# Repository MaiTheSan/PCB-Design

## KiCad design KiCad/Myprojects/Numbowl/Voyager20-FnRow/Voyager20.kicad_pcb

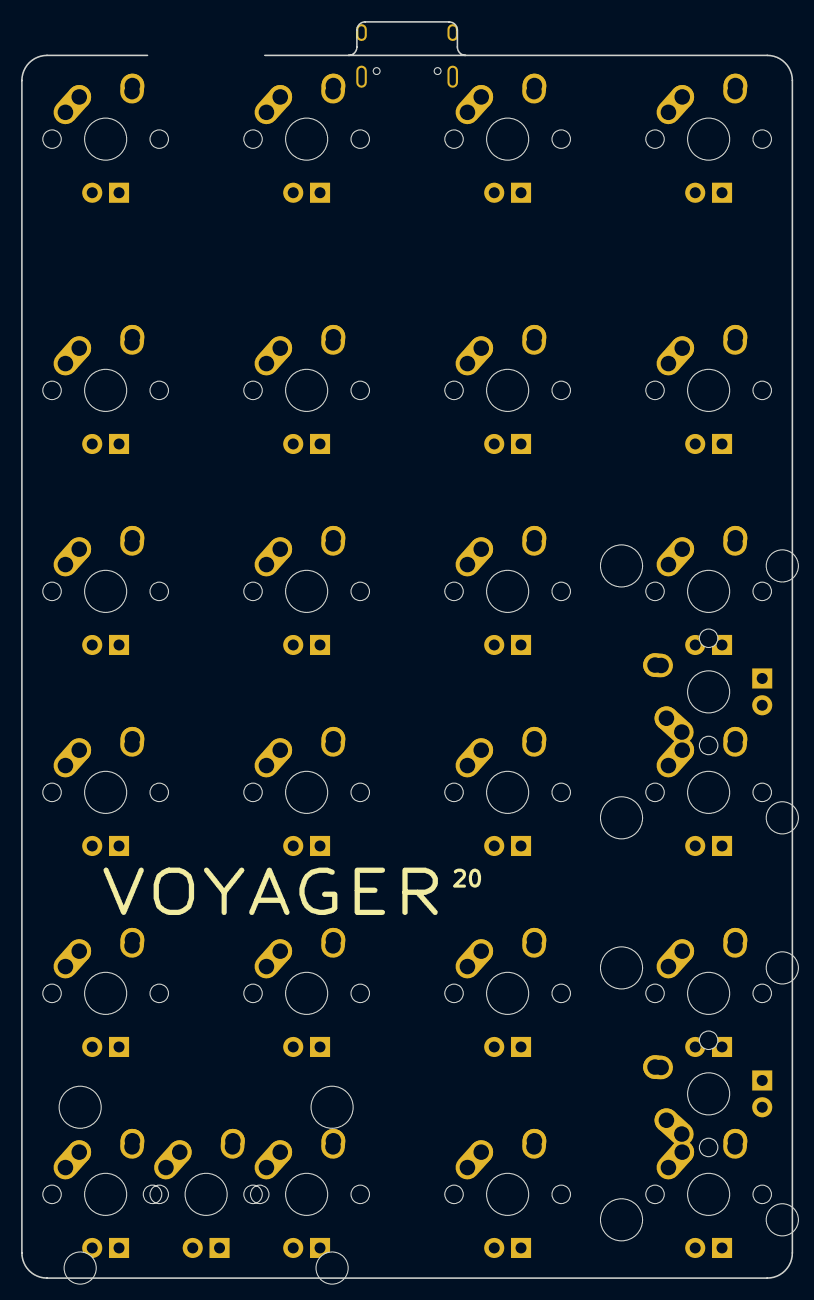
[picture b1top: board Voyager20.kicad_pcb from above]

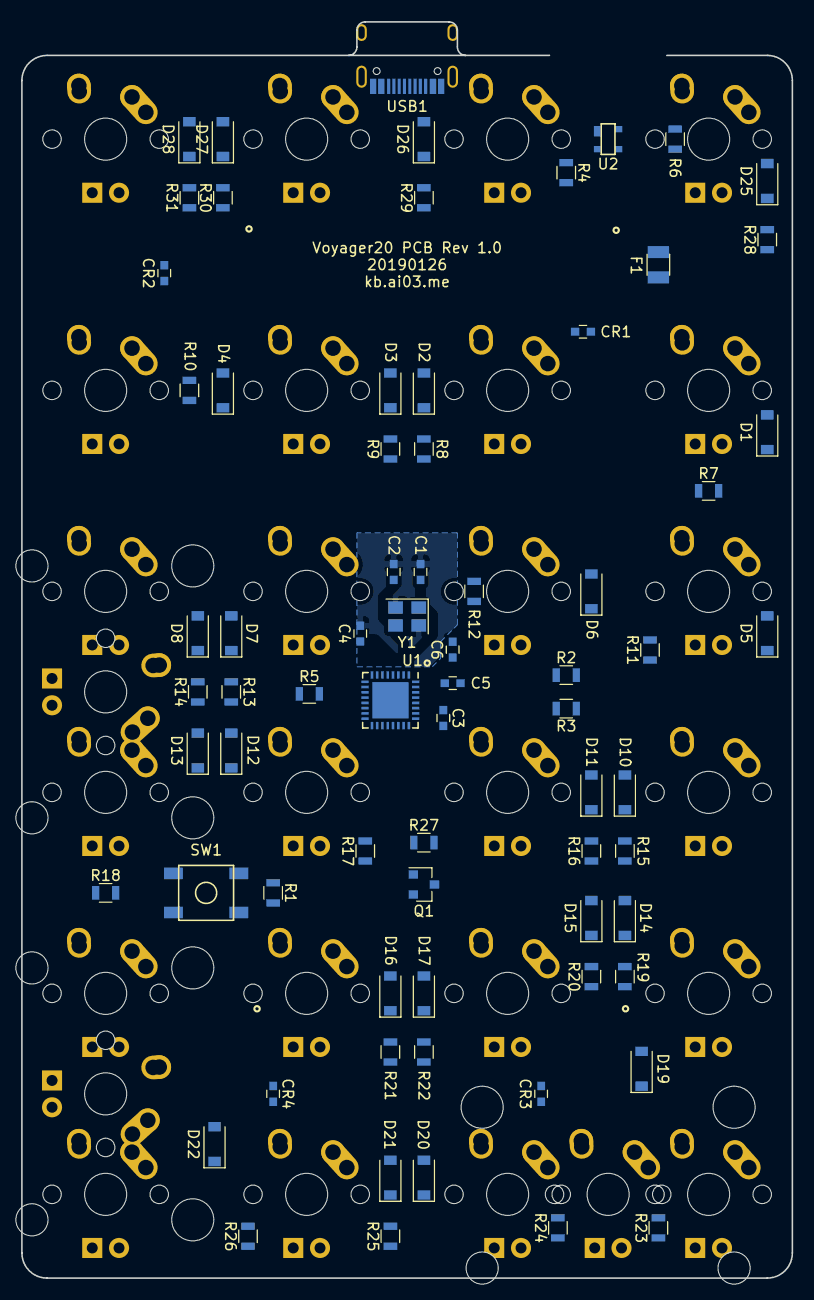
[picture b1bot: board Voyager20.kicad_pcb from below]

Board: 2 copper layers, 73.0 x 119.1 mm, 99 parts (72 on the bottom side), 75 nets, no tracks yet.

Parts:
C1, C2: 22p; C_0603
C3: 1uF; C_0603
C4, C5: 0.1u; C_0603
C6: 4.7u; C_0603
CR1, CR2, CR3, CR4: 0.1u; C_0603
D1, D2, D3, D4, D5, D6, D7, D8, D10, D11, D12, D13, D14, D15, D16, D17, D19, D20, D21, D22, D25, D26, D27, D28: SOD-123; D_SOD-123
F1: 500mA; Fuse_SMD1206_Reflow
MX1, MX2, MX3, MX4, MX5, MX6, MX7, MX8, MX9, MX10, MX11, MX12, MX13, MX14, MX15, MX16, MX17, MX18, MX19, MX20, MX21, MX22, MX23, MX24: MX-1U
MX-E-1, MX-E-2, MX-E-3: MX-2U; MX-2U-ReversedStabilizers
Q1: Q_NPN_BEC; SOT-23
R1, R5: 10k; R_0805
R2, R3: 22; R_0805
R4, R6: 5.1k; R_0805
R7, R8, R9, R10, R11, R12, R13, R14, R15, R16, R17, R18, R19, R20, R21, R22, R23, R24, R25, R26, R27, R28, R29, R30, R31: 1k; R_0805
SW1: SW_Push; SKQG-1155865
U1: ATmega32U2-AU; QFN-32-1EP_5x5mm_Pitch0.5mm
U2: PRTR5V0U2X; SOT143B
USB1: HRO-TYPE-C-31-M-12; HRO-TYPE-C-31-M-12-Assembly
Y1: 16MHz; Crystal_SMD_3225-4pin_3.2x2.5mm

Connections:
+5V: C4.1, C5.1, C6.1, CR1.1, CR2.1, CR3.1, CR4.1, F1.1, MX1.3, MX2.3, MX3.3, MX4.3, MX5.3, MX6.3, MX7.3, MX8.3, MX9.3, MX10.3, MX11.3, MX12.3, MX13.3, MX14.3, MX15.3, MX16.3, MX17.3, MX18.3, MX19.3, MX20.3, MX21.3, MX22.3, MX23.3, MX24.3, MX-E-1.3, MX-E-2.3, MX-E-3.3, R1.1, U1.4, U1.31, U1.32
COL0: MX1.1, MX5.1, MX9.1, MX13.1, MX17.1, MX21.1, MX-E-3.1, U1.26
COL1: MX2.1, MX6.1, MX10.1, MX14.1, MX18.1, MX22.1, U1.25
COL2: MX3.1, MX7.1, MX11.1, MX15.1, MX19.1, MX23.1, U1.17
COL3: MX4.1, MX8.1, MX12.1, MX16.1, MX20.1, MX24.1, MX-E-1.1, MX-E-2.1, U1.16
D+: R3.2, U1.29
D-: R2.1, U1.30
GND: C1.2, C2.2, C3.2, C4.2, C5.2, C6.2, CR1.2, CR2.2, CR3.2, CR4.2, Q1.2, R4.2, R5.1, R6.2, SW1.1, U1.3, U1.28, U2.1, USB1.1, USB1.12, USB1.13, Y1.2, Y1.4
LEDGND: Q1.3, R7.2, R8.2, R9.2, R10.2, R11.2, R12.2, R13.2, R14.2, R15.2, R16.2, R17.2, R18.2, R19.2, R20.2, R21.2, R22.2, R23.2, R24.2, R25.2, R26.2, R28.2, R29.2, R30.2, R31.2
unnamed: C1.1, U1.1, Y1.1
unnamed: C2.1, U1.2, Y1.3
unnamed: C3.1, U1.27
unnamed: D1.2, MX1.2
unnamed: D2.2, MX2.2
unnamed: D3.2, MX3.2
unnamed: D4.2, MX4.2
unnamed: D5.2, MX5.2
unnamed: D6.2, MX6.2
unnamed: D7.2, MX7.2
unnamed: D8.2, MX8.2
unnamed: D10.2, MX9.2
unnamed: D11.2, MX10.2
unnamed: D12.2, MX11.2
unnamed: D13.2, MX12.2, MX-E-1.2
unnamed: D14.2, MX13.2
unnamed: D15.2, MX14.2
unnamed: D16.2, MX15.2
unnamed: D17.2, MX16.2
unnamed: D19.2, MX17.2, MX-E-3.2
unnamed: D20.2, MX18.2
unnamed: D21.2, MX19.2
unnamed: D22.2, MX20.2, MX-E-2.2
unnamed: D25.2, MX21.2
unnamed: D26.2, MX22.2
unnamed: D27.2, MX23.2
unnamed: D28.2, MX24.2
unnamed: MX1.4, R7.1
unnamed: MX2.4, R8.1
unnamed: MX3.4, R9.1
unnamed: MX4.4, R10.1
unnamed: MX5.4, R11.1
unnamed: MX6.4, R12.1
unnamed: MX7.4, R13.1
unnamed: MX8.4, R14.1
unnamed: MX9.4, R15.1
unnamed: MX10.4, R16.1
unnamed: MX11.4, R17.1
unnamed: MX13.4, R19.1
unnamed: MX14.4, R20.1
unnamed: MX15.4, R21.1
unnamed: MX16.4, R22.1
unnamed: MX18.4, R24.1
unnamed: MX19.4, R25.1
unnamed: MX21.4, R28.1
unnamed: MX22.4, R29.1
unnamed: MX23.4, R30.1
unnamed: MX24.4, R31.1
unnamed: MX12.4, MX-E-1.4, R18.1
unnamed: MX20.4, MX-E-2.4, R26.1
unnamed: MX17.4, MX-E-3.4, R23.1
unnamed: Q1.1, R27.1
unnamed: R1.2, SW1.2, U1.24
unnamed: R2.2, U2.3, USB1.5, USB1.7
unnamed: R3.1, U2.2, USB1.6, USB1.8
unnamed: R4.1, USB1.10
unnamed: R5.2, U1.13
unnamed: R6.1, USB1.4
unnamed: R27.2, U1.21
ROW0: D1.1, D2.1, D3.1, D4.1, U1.7
ROW1: D5.1, D6.1, D7.1, D8.1, U1.8
ROW2: D10.1, D11.1, D12.1, D13.1, U1.23
ROW3: D14.1, D15.1, D16.1, D17.1, U1.22
ROW4: D19.1, D20.1, D21.1, D22.1, U1.20
ROWFN: D25.1, D26.1, D27.1, D28.1, U1.9
VCC: F1.2, U2.4, USB1.2, USB1.11

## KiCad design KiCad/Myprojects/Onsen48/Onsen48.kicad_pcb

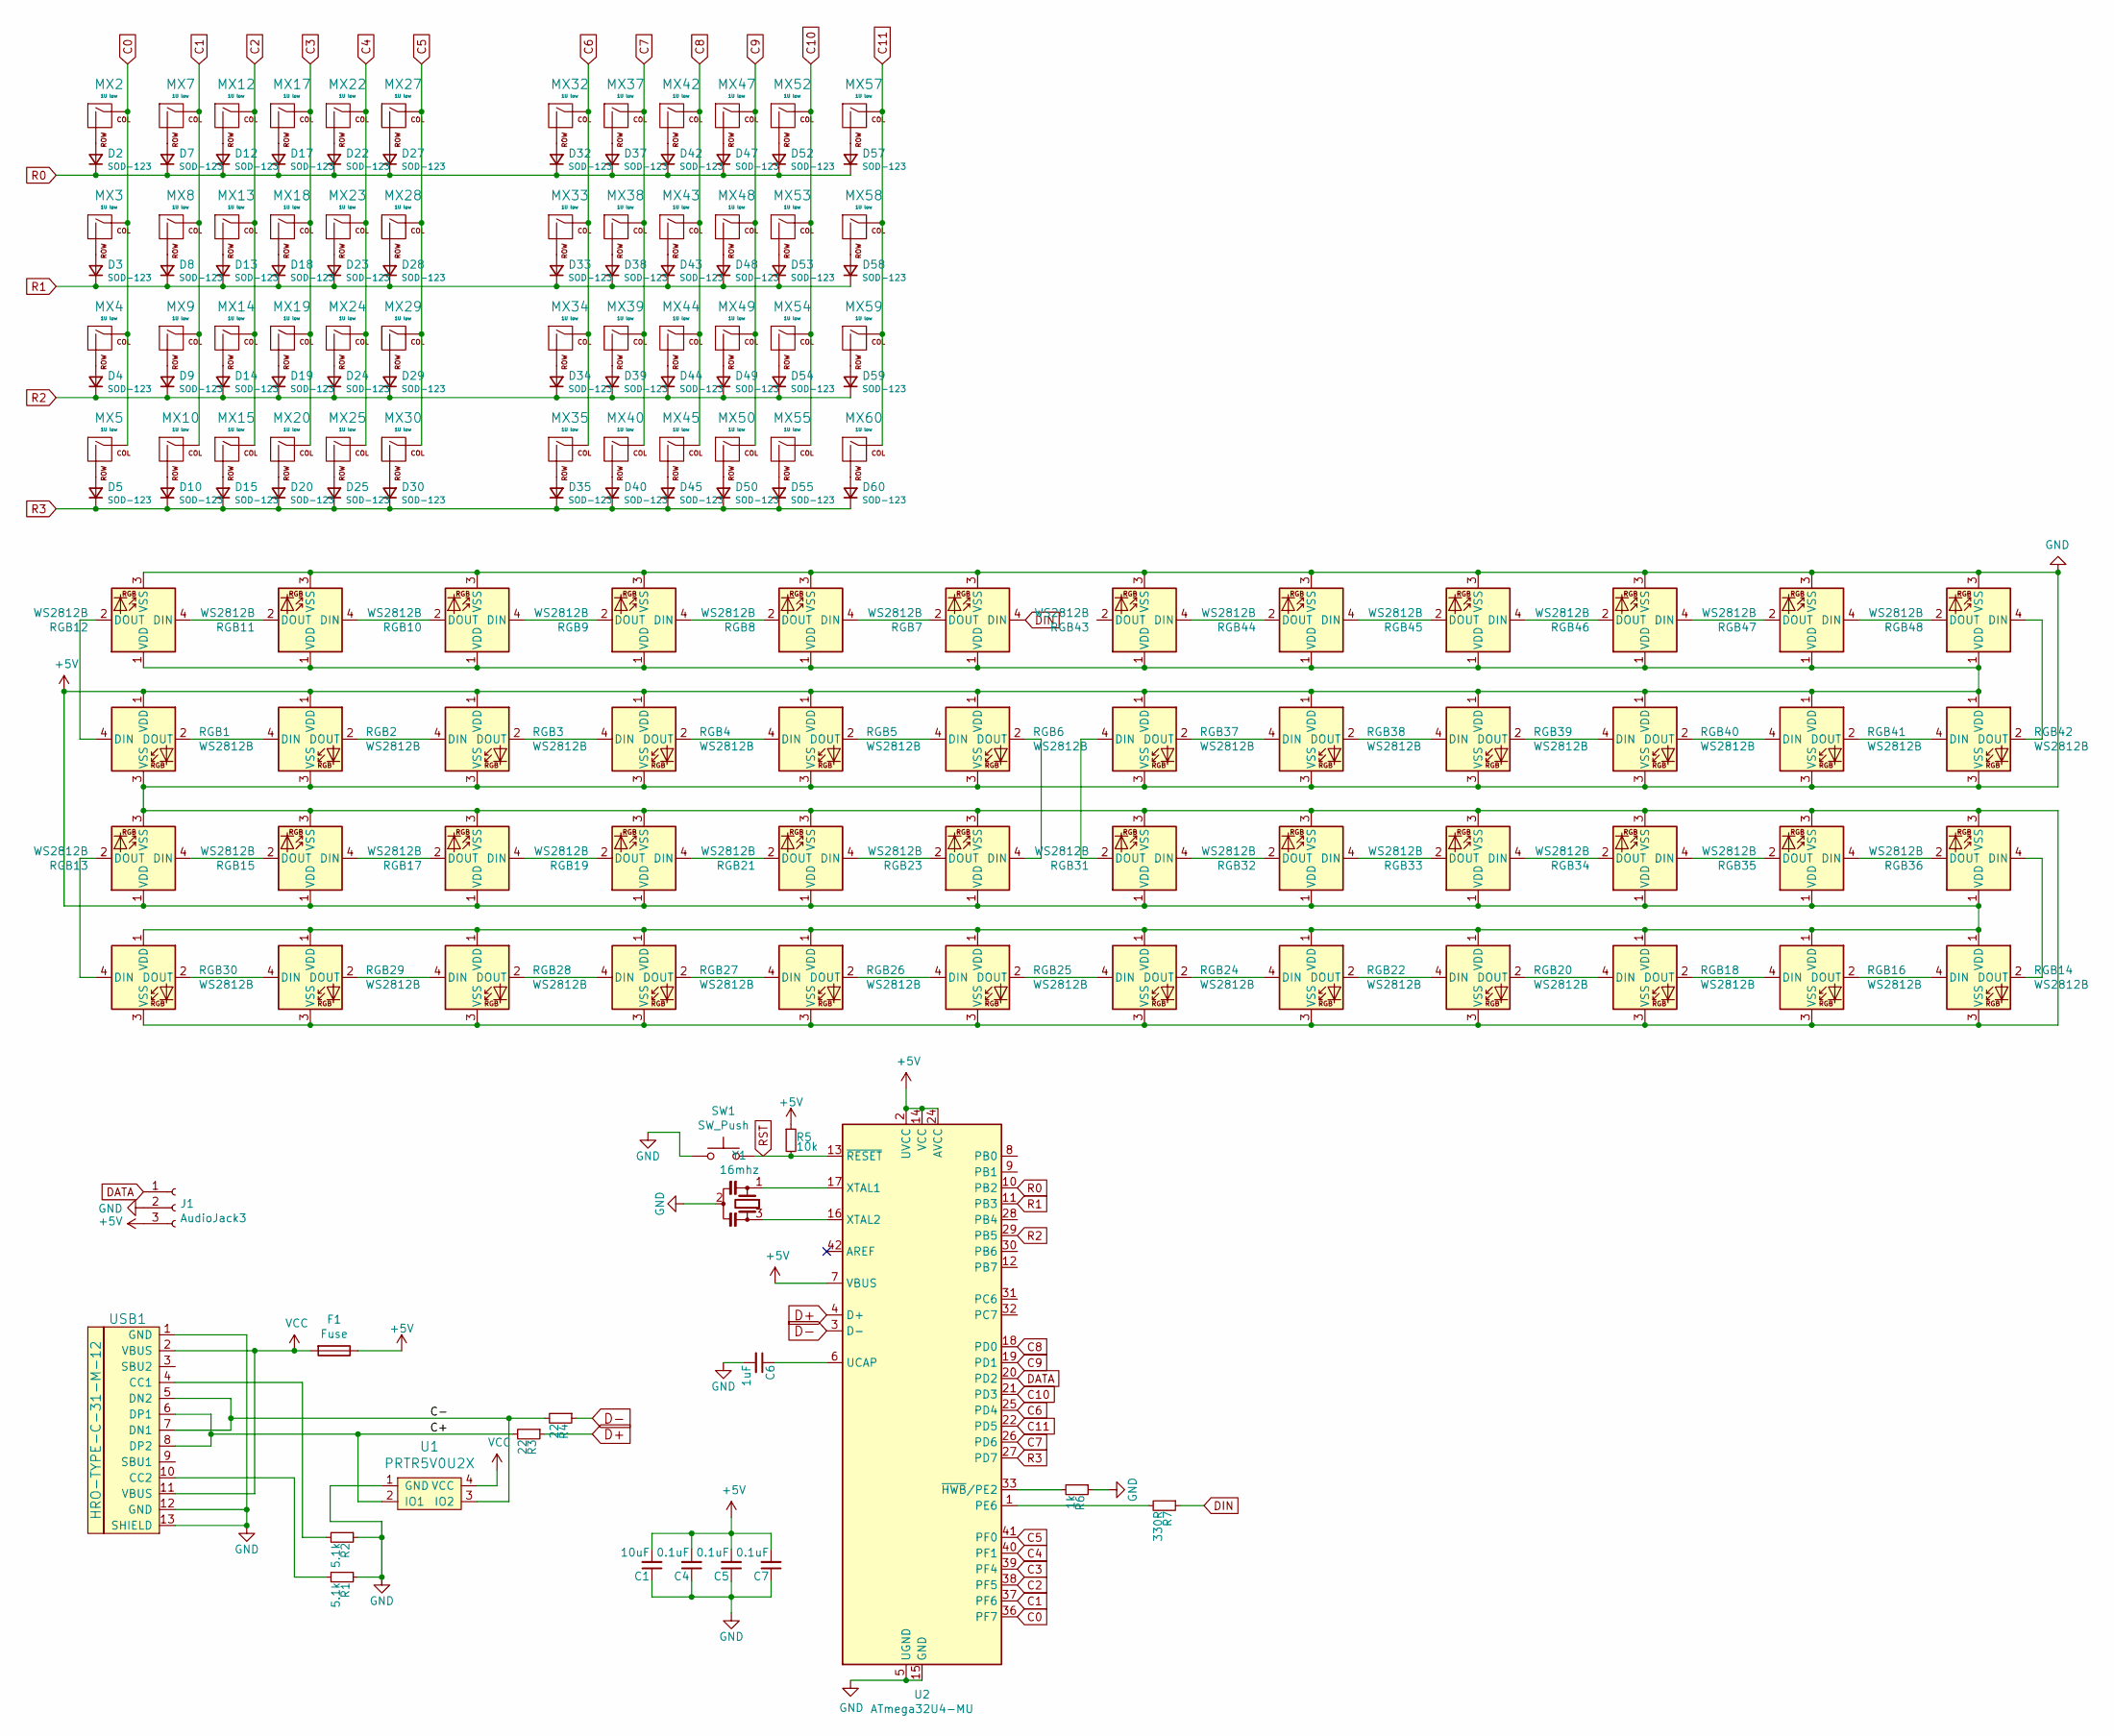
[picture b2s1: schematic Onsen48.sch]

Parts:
C1: 10uF; C_0603
C4, C5, C7: 0.1uF; C_0603
C6: 1uF; C_0603
D2, D3, D4, D5, D7, D8, D9, D10, D12, D13, D14, D15, D17, D18, D19, D20, D22, D23, D24, D25, D27, D28, D29, D30, D32, D33, D34, D35, D37, D38, D39, D40, D42, D43, D44, D45, D47, D48, D49, D50, D52, D53, D54, D55, D57, D58, D59, D60: SOD-123; D_SOD-123
F1: Fuse; Fuse_SMD1206_Reflow
J1: AudioJack3; PJ-3200B-4A-Assembly
MX2, MX3, MX4, MX5, MX7, MX8, MX9, MX10, MX12, MX13, MX14, MX15, MX17, MX18, MX19, MX20, MX22, MX23, MX24, MX25, MX27, MX28, MX29, MX30, MX32, MX33, MX34, MX35, MX37, MX38, MX39, MX40, MX42, MX43, MX44, MX45, MX47, MX48, MX49, MX50, MX52, MX53, MX54, MX55, MX57, MX58, MX59, MX60: 1U low; Kailh_socket_PG1350
R1, R2: 5.1k; R_0805
R3, R4: 22; R_0805
R5: 10k; R_0805
R6: 1k; R_0805
R7: 330R; R_0805
RGB1, RGB2, RGB3, RGB4, RGB5, RGB6, RGB14, RGB16, RGB18, RGB20, RGB22, RGB24, RGB25, RGB26, RGB27, RGB28, RGB29, RGB30, RGB37, RGB38, RGB39, RGB40, RGB41, RGB42: WS2812B; RGB-6028
RGB7, RGB8, RGB9, RGB10, RGB11, RGB12, RGB13, RGB15, RGB17, RGB19, RGB21, RGB23, RGB31, RGB32, RGB33, RGB34, RGB35, RGB36, RGB43, RGB44, RGB45, RGB46, RGB47, RGB48: WS2812B; RGB-6028_FLIPPED
SW1: SW_Push; SKQG-1155865
U1: PRTR5V0U2X; SOT143B
U2: ATmega32U4-MU; QFN-44-1EP_7x7mm_P0.5mm_EP5.15x5.15mm
USB1: HRO-TYPE-C-31-M-12; HRO-TYPE-C-31-M-12-Assembly
Y1: 16mhz; Resonator_SMD_muRata_CSTxExxV-3Pin_3.0x1.1mm

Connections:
+5V: C1.2, C4.2, C5.2, C7.2, F1.1, J1.3, R5.1, RGB1.1 (VDD), RGB2.1 (VDD), RGB3.1 (VDD), RGB4.1 (VDD), RGB5.1 (VDD), RGB6.1 (VDD), RGB7.1 (VDD), RGB8.1 (VDD), RGB9.1 (VDD), RGB10.1 (VDD), RGB11.1 (VDD), RGB12.1 (VDD), RGB13.1 (VDD), RGB14.1 (VDD), RGB15.1 (VDD), RGB16.1 (VDD), RGB17.1 (VDD), RGB18.1 (VDD), RGB19.1 (VDD), RGB20.1 (VDD), RGB21.1 (VDD), RGB22.1 (VDD), RGB23.1 (VDD), RGB24.1 (VDD), RGB25.1 (VDD), RGB26.1 (VDD), RGB27.1 (VDD), RGB28.1 (VDD), RGB29.1 (VDD), RGB30.1 (VDD), RGB31.1 (VDD), RGB32.1 (VDD), RGB33.1 (VDD), RGB34.1 (VDD), RGB35.1 (VDD), RGB36.1 (VDD), RGB37.1 (VDD), RGB38.1 (VDD), RGB39.1 (VDD), RGB40.1 (VDD), RGB41.1 (VDD), RGB42.1 (VDD), RGB43.1 (VDD), RGB44.1 (VDD), RGB45.1 (VDD), RGB46.1 (VDD), RGB47.1 (VDD), RGB48.1 (VDD), U2.2 (UVCC), U2.7 (VBUS), U2.14 (VCC), U2.24 (AVCC), U2.34 (VCC), U2.44 (AVCC)
/C+: R3.2, U1.2 (IO1), USB1.6 (DP1), USB1.8 (DP2)
/C-: R4.2, U1.3 (IO2), USB1.5 (DN2), USB1.7 (DN1)
C0: MX2.1 (COL), MX3.1 (COL), MX4.1 (COL), MX5.1 (COL), U2.36 (PF7)
C1: MX7.1 (COL), MX8.1 (COL), MX9.1 (COL), MX10.1 (COL), U2.37 (PF6)
C2: MX12.1 (COL), MX13.1 (COL), MX14.1 (COL), MX15.1 (COL), U2.38 (PF5)
C3: MX17.1 (COL), MX18.1 (COL), MX19.1 (COL), MX20.1 (COL), U2.39 (PF4)
C4: MX22.1 (COL), MX23.1 (COL), MX24.1 (COL), MX25.1 (COL), U2.40 (PF1)
C5: MX27.1 (COL), MX28.1 (COL), MX29.1 (COL), MX30.1 (COL), U2.41 (PF0)
C6: MX32.1 (COL), MX33.1 (COL), MX34.1 (COL), MX35.1 (COL), U2.25 (PD4)
C7: MX37.1 (COL), MX38.1 (COL), MX39.1 (COL), MX40.1 (COL), U2.26 (PD6)
C8: MX42.1 (COL), MX43.1 (COL), MX44.1 (COL), MX45.1 (COL), U2.18 (PD0)
C9: MX47.1 (COL), MX48.1 (COL), MX49.1 (COL), MX50.1 (COL), U2.19 (PD1)
C10: MX52.1 (COL), MX53.1 (COL), MX54.1 (COL), MX55.1 (COL), U2.21 (PD3)
C11: MX57.1 (COL), MX58.1 (COL), MX59.1 (COL), MX60.1 (COL), U2.22 (PD5)
D+: R3.1, U2.4 (D+)
D-: R4.1, U2.3 (D-)
DATA: J1.1, U2.20 (PD2)
DIN: R7.1, RGB7.4 (DIN)
GND: C1.1, C4.1, C5.1, C6.2, C7.1, J1.2, R1.1, R2.1, R6.1, RGB1.3 (VSS), RGB2.3 (VSS), RGB3.3 (VSS), RGB4.3 (VSS), RGB5.3 (VSS), RGB6.3 (VSS), RGB7.3 (VSS), RGB8.3 (VSS), RGB9.3 (VSS), RGB10.3 (VSS), RGB11.3 (VSS), RGB12.3 (VSS), RGB13.3 (VSS), RGB14.3 (VSS), RGB15.3 (VSS), RGB16.3 (VSS), RGB17.3 (VSS), RGB18.3 (VSS), RGB19.3 (VSS), RGB20.3 (VSS), RGB21.3 (VSS), RGB22.3 (VSS), RGB23.3 (VSS), RGB24.3 (VSS), RGB25.3 (VSS), RGB26.3 (VSS), RGB27.3 (VSS), RGB28.3 (VSS), RGB29.3 (VSS), RGB30.3 (VSS), RGB31.3 (VSS), RGB32.3 (VSS), RGB33.3 (VSS), RGB34.3 (VSS), RGB35.3 (VSS), RGB36.3 (VSS), RGB37.3 (VSS), RGB38.3 (VSS), RGB39.3 (VSS), RGB40.3 (VSS), RGB41.3 (VSS), RGB42.3 (VSS), RGB43.3 (VSS), RGB44.3 (VSS), RGB45.3 (VSS), RGB46.3 (VSS), RGB47.3 (VSS), RGB48.3 (VSS), SW1.1, U1.1 (GND), U2.5 (UGND), U2.15 (GND), U2.23 (GND), U2.35 (GND), U2.43 (GND), U2.45 (GND), USB1.1 (GND), USB1.12 (GND), USB1.13 (SHIELD), Y1.2
unnamed: C6.1, U2.6 (UCAP)
unnamed: D2.2 (A), MX2.2 (ROW)
unnamed: D3.2 (A), MX3.2 (ROW)
unnamed: D4.2 (A), MX4.2 (ROW)
unnamed: D5.2 (A), MX5.2 (ROW)
unnamed: D7.2 (A), MX7.2 (ROW)
unnamed: D8.2 (A), MX8.2 (ROW)
unnamed: D9.2 (A), MX9.2 (ROW)
unnamed: D10.2 (A), MX10.2 (ROW)
unnamed: D12.2 (A), MX12.2 (ROW)
unnamed: D13.2 (A), MX13.2 (ROW)
unnamed: D14.2 (A), MX14.2 (ROW)
unnamed: D15.2 (A), MX15.2 (ROW)
unnamed: D17.2 (A), MX17.2 (ROW)
unnamed: D18.2 (A), MX18.2 (ROW)
unnamed: D19.2 (A), MX19.2 (ROW)
unnamed: D20.2 (A), MX20.2 (ROW)
unnamed: D22.2 (A), MX22.2 (ROW)
unnamed: D23.2 (A), MX23.2 (ROW)
unnamed: D24.2 (A), MX24.2 (ROW)
unnamed: D25.2 (A), MX25.2 (ROW)
unnamed: D27.2 (A), MX27.2 (ROW)
unnamed: D28.2 (A), MX28.2 (ROW)
unnamed: D29.2 (A), MX29.2 (ROW)
unnamed: D30.2 (A), MX30.2 (ROW)
unnamed: D32.2 (A), MX32.2 (ROW)
unnamed: D33.2 (A), MX33.2 (ROW)
unnamed: D34.2 (A), MX34.2 (ROW)
unnamed: D35.2 (A), MX35.2 (ROW)
unnamed: D37.2 (A), MX37.2 (ROW)
unnamed: D38.2 (A), MX38.2 (ROW)
unnamed: D39.2 (A), MX39.2 (ROW)
unnamed: D40.2 (A), MX40.2 (ROW)
unnamed: D42.2 (A), MX42.2 (ROW)
unnamed: D43.2 (A), MX43.2 (ROW)
unnamed: D44.2 (A), MX44.2 (ROW)
unnamed: D45.2 (A), MX45.2 (ROW)
unnamed: D47.2 (A), MX47.2 (ROW)
unnamed: D48.2 (A), MX48.2 (ROW)
unnamed: D49.2 (A), MX49.2 (ROW)
unnamed: D50.2 (A), MX50.2 (ROW)
unnamed: D52.2 (A), MX52.2 (ROW)
unnamed: D53.2 (A), MX53.2 (ROW)
unnamed: D54.2 (A), MX54.2 (ROW)
unnamed: D55.2 (A), MX55.2 (ROW)
unnamed: D57.2 (A), MX57.2 (ROW)
unnamed: D58.2 (A), MX58.2 (ROW)
unnamed: D59.2 (A), MX59.2 (ROW)
unnamed: D60.2 (A), MX60.2 (ROW)
unnamed: R1.2, USB1.10 (CC2)
unnamed: R2.2, USB1.4 (CC1)
unnamed: R6.2, U2.33 (~HWB~/PE2)
unnamed: R7.2, U2.1 (PE6)
unnamed: RGB1.2 (DOUT), RGB2.4 (DIN)
unnamed: RGB1.4 (DIN), RGB12.2 (DOUT)
unnamed: RGB2.2 (DOUT), RGB3.4 (DIN)
unnamed: RGB3.2 (DOUT), RGB4.4 (DIN)
unnamed: RGB4.2 (DOUT), RGB5.4 (DIN)
unnamed: RGB5.2 (DOUT), RGB6.4 (DIN)
unnamed: RGB7.2 (DOUT), RGB8.4 (DIN)
unnamed: RGB8.2 (DOUT), RGB9.4 (DIN)
unnamed: RGB10.2 (DOUT), RGB11.4 (DIN)
unnamed: RGB9.2 (DOUT), RGB10.4 (DIN)
unnamed: RGB11.2 (DOUT), RGB12.4 (DIN)
unnamed: RGB13.2 (DOUT), RGB30.4 (DIN)
unnamed: RGB13.4 (DIN), RGB15.2 (DOUT)
unnamed: RGB14.2 (DOUT), RGB36.4 (DIN)
unnamed: RGB14.4 (DIN), RGB16.2 (DOUT)
unnamed: RGB15.4 (DIN), RGB17.2 (DOUT)
unnamed: RGB16.4 (DIN), RGB18.2 (DOUT)
unnamed: RGB17.4 (DIN), RGB19.2 (DOUT)
unnamed: RGB18.4 (DIN), RGB20.2 (DOUT)
unnamed: RGB19.4 (DIN), RGB21.2 (DOUT)
unnamed: RGB20.4 (DIN), RGB22.2 (DOUT)
unnamed: RGB21.4 (DIN), RGB23.2 (DOUT)
unnamed: RGB22.4 (DIN), RGB24.2 (DOUT)
unnamed: RGB6.2 (DOUT), RGB23.4 (DIN)
unnamed: RGB24.4 (DIN), RGB25.2 (DOUT)
unnamed: RGB25.4 (DIN), RGB26.2 (DOUT)
unnamed: RGB26.4 (DIN), RGB27.2 (DOUT)
unnamed: RGB27.4 (DIN), RGB28.2 (DOUT)
unnamed: RGB28.4 (DIN), RGB29.2 (DOUT)
unnamed: RGB29.4 (DIN), RGB30.2 (DOUT)
unnamed: RGB31.2 (DOUT), RGB37.4 (DIN)
unnamed: RGB31.4 (DIN), RGB32.2 (DOUT)
unnamed: RGB32.4 (DIN), RGB33.2 (DOUT)
unnamed: RGB33.4 (DIN), RGB34.2 (DOUT)
unnamed: RGB34.4 (DIN), RGB35.2 (DOUT)
unnamed: RGB35.4 (DIN), RGB36.2 (DOUT)
unnamed: RGB37.2 (DOUT), RGB38.4 (DIN)
unnamed: RGB38.2 (DOUT), RGB39.4 (DIN)
unnamed: RGB39.2 (DOUT), RGB40.4 (DIN)
unnamed: RGB40.2 (DOUT), RGB41.4 (DIN)
unnamed: RGB41.2 (DOUT), RGB42.4 (DIN)
unnamed: RGB42.2 (DOUT), RGB48.4 (DIN)
unnamed: RGB43.4 (DIN), RGB44.2 (DOUT)
unnamed: RGB44.4 (DIN), RGB45.2 (DOUT)
unnamed: RGB45.4 (DIN), RGB46.2 (DOUT)
unnamed: RGB46.4 (DIN), RGB47.2 (DOUT)
unnamed: RGB47.4 (DIN), RGB48.2 (DOUT)
unnamed: U2.16 (XTAL2), Y1.3
unnamed: U2.17 (XTAL1), Y1.1
R0: D2.1 (K), D7.1 (K), D12.1 (K), D17.1 (K), D22.1 (K), D27.1 (K), D32.1 (K), D37.1 (K), D42.1 (K), D47.1 (K), D52.1 (K), D57.1 (K), U2.10 (PB2)
R1: D3.1 (K), D8.1 (K), D13.1 (K), D18.1 (K), D23.1 (K), D28.1 (K), D33.1 (K), D38.1 (K), D43.1 (K), D48.1 (K), D53.1 (K), D58.1 (K), U2.11 (PB3)
R2: D4.1 (K), D9.1 (K), D14.1 (K), D19.1 (K), D24.1 (K), D29.1 (K), D34.1 (K), D39.1 (K), D44.1 (K), D49.1 (K), D54.1 (K), D59.1 (K), U2.29 (PB5)
R3: D5.1 (K), D10.1 (K), D15.1 (K), D20.1 (K), D25.1 (K), D30.1 (K), D35.1 (K), D40.1 (K), D45.1 (K), D50.1 (K), D55.1 (K), D60.1 (K), U2.27 (PD7)
RST: R5.2, SW1.2, U2.13 (~RESET)
VCC: F1.2, U1.4 (VCC), USB1.2 (VBUS), USB1.11 (VBUS)

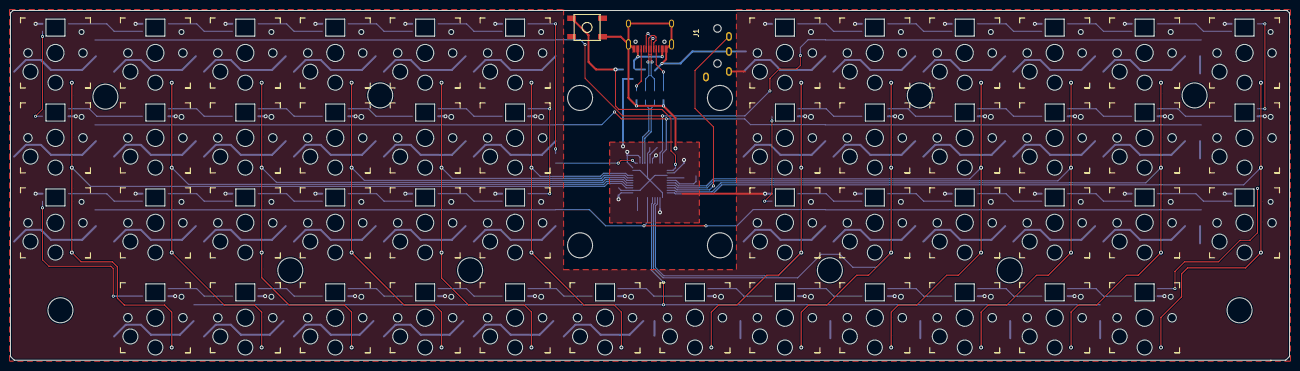
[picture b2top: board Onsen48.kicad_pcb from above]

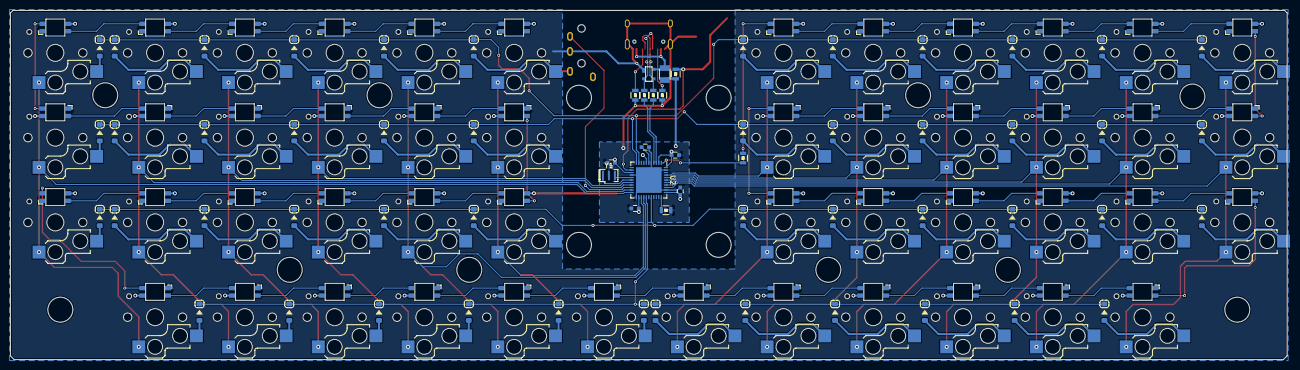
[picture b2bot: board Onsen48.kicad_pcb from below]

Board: 2 copper layers, 256.0 x 70.0 mm, 163 parts (112 on the bottom side), 128 nets.

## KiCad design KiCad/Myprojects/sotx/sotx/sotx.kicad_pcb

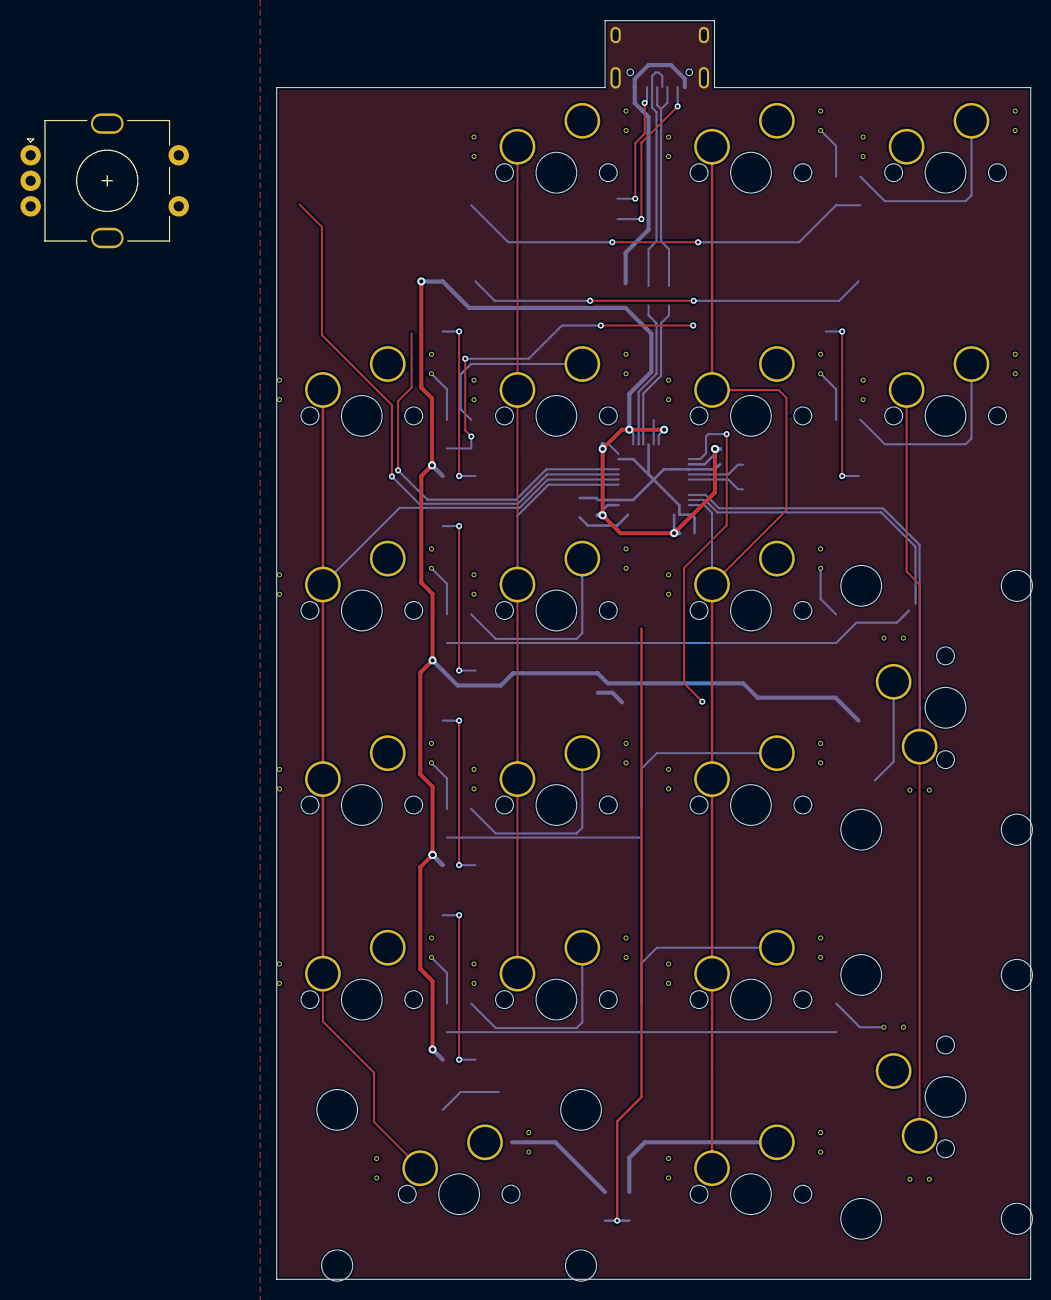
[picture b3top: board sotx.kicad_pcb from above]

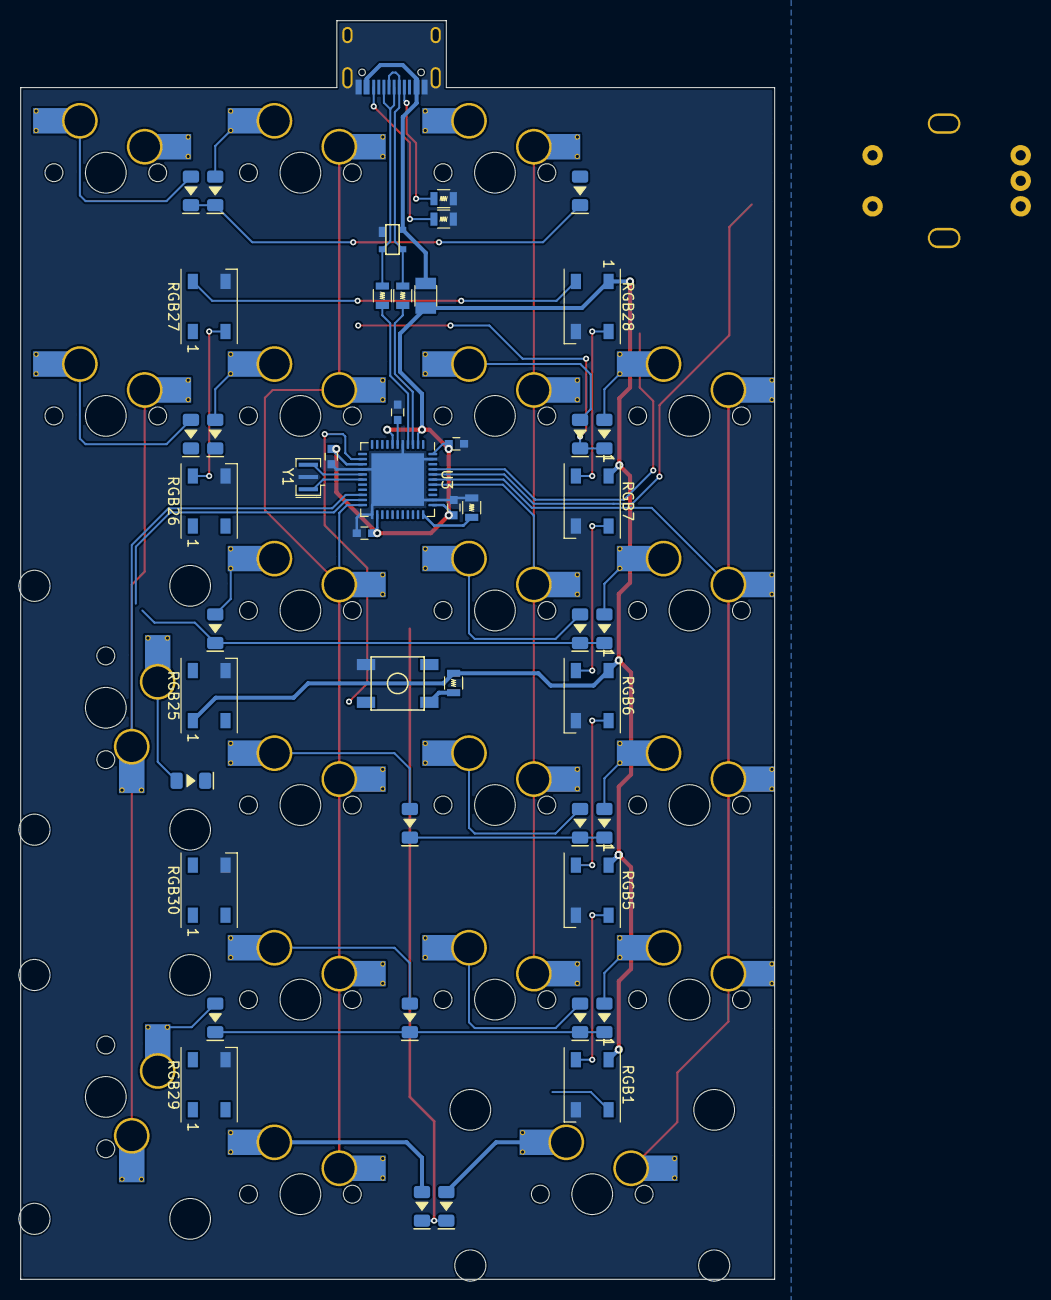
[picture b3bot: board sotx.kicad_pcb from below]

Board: 2 copper layers, 73.8 x 123.2 mm, 68 parts (47 on the bottom side), 53 nets.

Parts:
C1: 10uF; C_0603
C4, C5, C7: 0.1uF; C_0603
C6: 1uF; C_0603
D1, D2, D3, D4, D5, D6, D7, D8, D9, D10, D11, D12, D13, D14, D15, D17, D19, D20, D21, D22: 1n4148W; DIODE_1206_SawnsProjects
F1: Fuse; Fuse_SMD1206_Reflow
MX2, MX3, MX4, MX5, MX6, MX7, MX8, MX9, MX10, MX11, MX12, MX13, MX14, MX17, MX19, MX21, MX22: 1U; MXOnly-1U-Hotswap-Sawns
MX15, MX16, MX20: 2U; MXOnly-2U-Hotswap-ReversedStabilizers-Sawns
R1, R2: 5.1k; R_0805
R3, R4: 22; R_0805
R5: 10k; R_0805
R6: 1k; R_0805
RGB1, RGB5, RGB6, RGB7, RGB25, RGB26, RGB27, RGB28, RGB29, RGB30: WS2812B; LED_WS2812B_PLCC4_5.0x5.0mm_P3.2mm
SW1: EC11; RotaryEncoder_Alps_EC11E-Switch_Vertical_H20mm_Center
SW2: SW_Push; SKQG-1155865
U2: PRTR5V0U2X; SOT143B
U3: ATmega32U4-MU; QFN-44-1EP_7x7mm_P0.5mm_EP5.15x5.15mm
USB1: HRO-TYPE-C-31-M-12; HRO-TYPE-C-31-M-12-Assembly
Y1: CSTCE16Mxx; Resonator_SMD_muRata_CSTxExxV-3Pin_3.0x1.1mm

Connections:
+5V: C1.2, C4.2, C5.2, C7.2, F1.1, R5.1, RGB1.1, RGB5.1, RGB6.1, RGB7.1, RGB25.1, RGB26.1, RGB27.1, RGB28.1, RGB29.1, RGB30.1, U3.2, U3.7, U3.14, U3.24, U3.34, U3.44
C0: MX5.1, MX9.1, MX10.1, MX17.1, MX20.1, U3.39
C1: MX2.1, MX6.1, MX11.1, MX12.1, MX19.1, U3.38
C2: MX3.1, MX7.1, MX13.1, MX14.1, MX21.1, MX22.1, U3.22
C3: MX4.1, MX8.1, MX15.1, MX16.1, U3.20
D+: R3.1, U3.4
D-: R4.1, U3.3
DG+: R3.2, U2.2, USB1.6, USB1.8
DG-: R4.2, U2.3, USB1.5, USB1.7
GND: C1.1, C4.1, C5.1, C6.2, C7.1, R1.1, R2.1, R6.1, RGB1.3, RGB5.3, RGB6.3, RGB7.3, RGB25.3, RGB26.3, RGB27.3, RGB28.3, RGB29.3, RGB30.3, SW2.1, U2.1, U3.5, U3.15, U3.23, U3.35, U3.43, U3.45, USB1.1, USB1.12, USB1.13, Y1.2
unnamed: C6.1, U3.6
unnamed: D1.2, MX16.2
unnamed: D2.2, MX2.2
unnamed: D3.2, MX3.2
unnamed: D4.2, MX4.2
unnamed: D5.2, MX5.2
unnamed: D6.2, MX6.2
unnamed: D7.2, MX7.2
unnamed: D8.2, MX8.2
unnamed: D9.2, MX9.2
unnamed: D10.2, MX10.2
unnamed: D11.2, MX11.2
unnamed: D12.2, MX12.2
unnamed: D13.2, MX13.2
unnamed: D14.2, MX14.2
unnamed: D15.2, MX15.2
unnamed: D17.2, MX17.2
unnamed: D19.2, MX19.2
unnamed: D20.2, MX20.2
unnamed: D21.2, MX21.2
unnamed: D22.2, MX22.2
unnamed: R1.2, USB1.4
unnamed: R2.2, USB1.10
unnamed: R6.2, U3.33
unnamed: RGB1.2, RGB5.4
unnamed: RGB5.2, RGB6.4
unnamed: RGB6.2, RGB7.4
unnamed: RGB25.2, RGB30.4
unnamed: RGB25.4, RGB26.2
unnamed: RGB26.4, RGB27.2
unnamed: RGB27.4, RGB28.2
unnamed: RGB7.2, RGB28.4
unnamed: RGB29.4, RGB30.2
unnamed: U3.16, Y1.3
unnamed: U3.17, Y1.1
R0: D2.1, D3.1, D4.1
R1: D5.1, D6.1, D7.1
R2: D9.1, D11.1, D13.1
R3: D10.1, D12.1, D14.1
R4: D1.1, D17.1, D19.1, D21.1
R5: D20.1, D22.1
RST: R5.2, SW2.2, U3.13
VCC: F1.2, U2.4, USB1.2, USB1.11
